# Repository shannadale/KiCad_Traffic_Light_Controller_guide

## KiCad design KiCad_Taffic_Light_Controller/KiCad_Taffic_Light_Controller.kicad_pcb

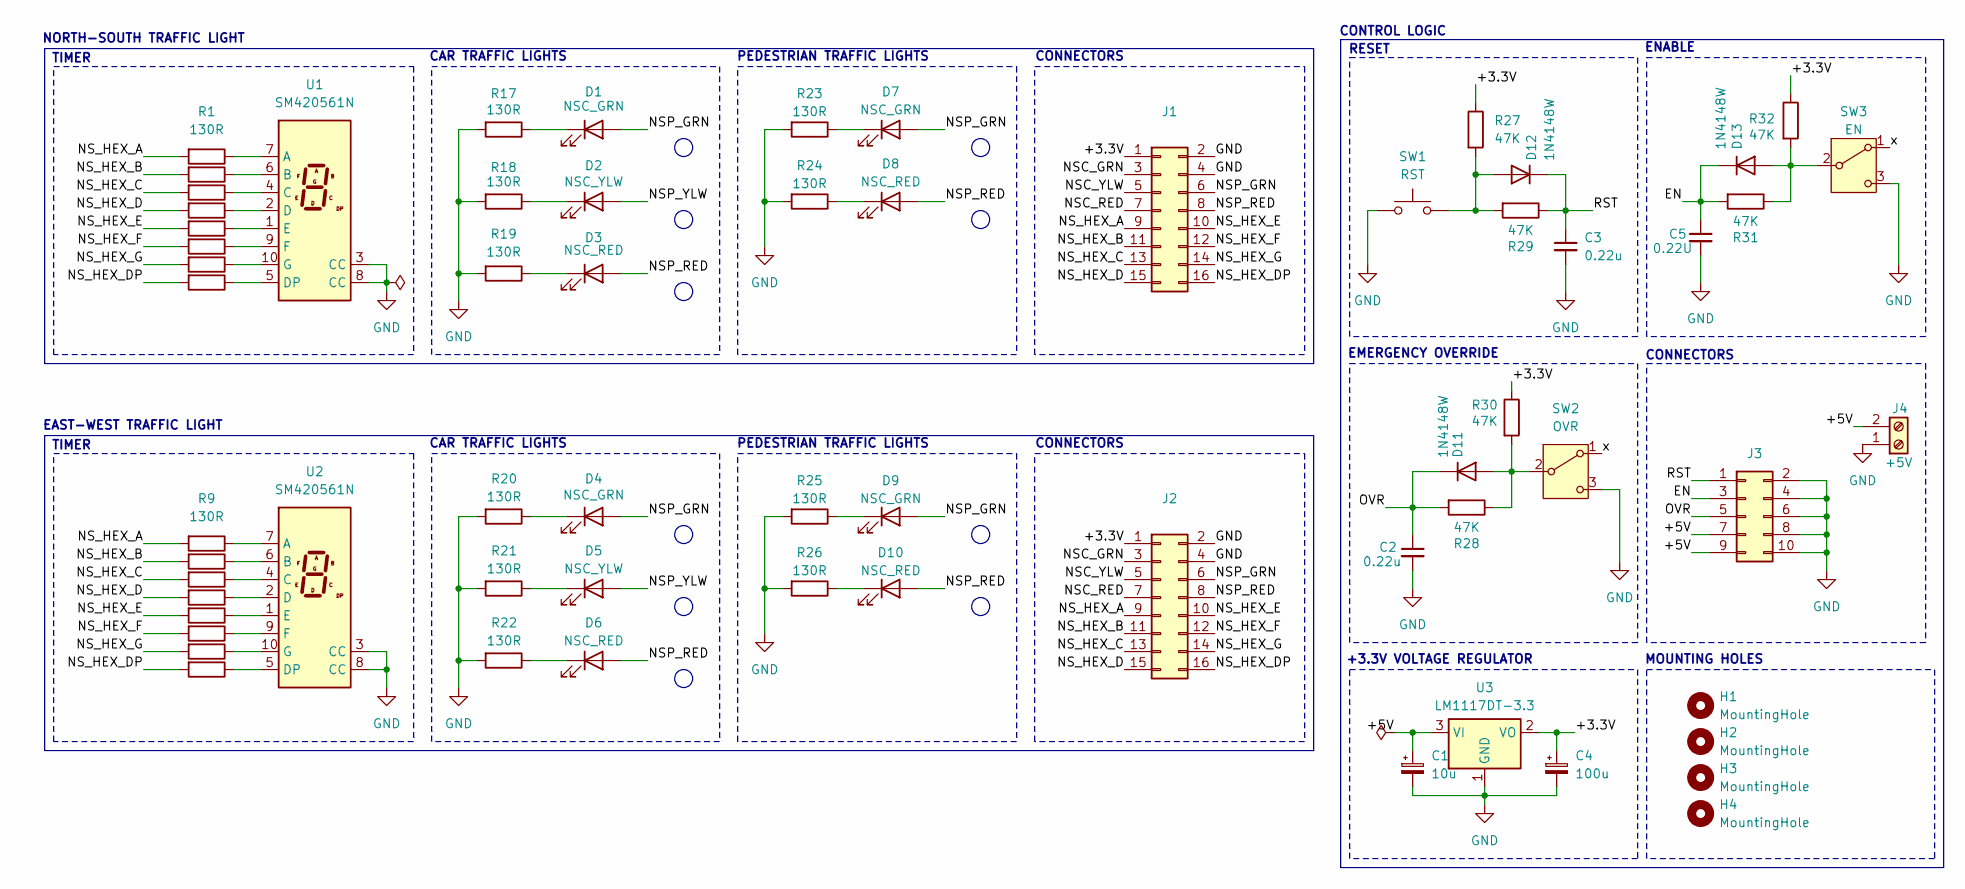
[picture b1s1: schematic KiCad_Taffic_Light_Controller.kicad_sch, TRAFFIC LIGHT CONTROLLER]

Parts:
C1: 10u; CP_Elec_4x5.3
C2, C3: 0.22u; C_1206_3216Metric_Pad1.33x1.80mm_HandSolder
C4: 100u; CP_Elec_6.3x5.8
C5: 0.22U; C_1206_3216Metric_Pad1.33x1.80mm_HandSolder
D1, D4, D7, D9: NSC_GRN; LED_D5.0mm
D2, D5: NSC_YLW; LED_D5.0mm
D3, D6, D8, D10: NSC_RED; LED_D5.0mm
D11, D12, D13: 1N4148W; D_SOD-123
H1, H2, H3, H4: MountingHole; MountingHole_2.2mm_M2
J1: NS Connector; PinHeader_2x08_P2.54mm_Vertical
J2: EW Connector; PinHeader_2x08_P2.54mm_Vertical
J3: Control Logic Connector; PinHeader_2x05_P2.54mm_Vertical
J4: +5V; Terminal_Block_5mm
R1, R2, R3, R4, R5, R6, R7, R8, R9, R10, R11, R12, R13, R14, R15, R16, R17, R18, R19, R20, R21, R22, R23, R24, R25, R26: 130R; R_1206_3216Metric_Pad1.30x1.75mm_HandSolder
R27, R28, R29, R30, R31, R32: 47K; R_1206_3216Metric_Pad1.30x1.75mm_HandSolder
SW1: RST; tact_switch_5mm
SW2: OVR; slide_switch_2.54mm
SW3: EN; slide_switch_2.54mm
U1, U2: SM420561N; 7SegmentLED_LTS6760_LTS6780
U3: LM1117DT-3.3; SOT-223

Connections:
/+3.3V: C4.1, J1.1, J2.1, R27.1, R30.1, R32.1, U3.2 (VO)
/+5V: C1.1, J3.7, J3.9, J4.2, U3.3 (VI)
/EN: C5.1, D13.1 (K), J3.3, R31.2
/NSC_GRN: J1.3, J2.3
/NSC_RED: J1.7, J2.7
/NSC_YLW: J1.5, J2.5
/NSP_GRN: D1.2 (A), D4.2 (A), D7.2 (A), D9.2 (A), J1.6, J2.6
/NSP_RED: D3.2 (A), D6.2 (A), D8.2 (A), D10.2 (A), J1.8, J2.8
/NSP_YLW: D2.2 (A), D5.2 (A)
/NS_HEX_A: J1.9, J2.9, R1.2, R9.2
/NS_HEX_B: J1.11, J2.11, R2.2, R10.2
/NS_HEX_C: J1.13, J2.13, R3.2, R11.2
/NS_HEX_D: J1.15, J2.15, R4.2, R12.2
/NS_HEX_DP: J1.16, J2.16, R8.2, R16.2
/NS_HEX_E: J1.10, J2.10, R5.2, R13.2
/NS_HEX_F: J1.12, J2.12, R6.2, R14.2
/NS_HEX_G: J1.14, J2.14, R7.2, R15.2
/OVR: C2.1, D11.1 (K), J3.5, R28.2
/RST: C3.1, D12.1 (K), J3.1, R29.1
/x: SW2.1 (A), SW3.1 (A)
GND: C1.2, C2.2, C3.2, C4.2, C5.2, J1.2, J1.4, J2.2, J2.4, J3.2, J3.4, J3.6, J3.8, J3.10, J4.1, R17.2, R18.2, R19.2, R20.2, R21.2, R22.2, R23.2, R24.2, R25.2, R26.2, SW1.1, SW2.3 (C), SW3.3 (C), U1.3 (CC), U1.8 (CC), U2.3 (CC), U2.8 (CC), U3.1 (GND)
unnamed: D1.1 (K), R17.1
unnamed: D2.1 (K), R18.1
unnamed: D3.1 (K), R19.1
unnamed: D4.1 (K), R20.1
unnamed: D5.1 (K), R21.1
unnamed: D6.1 (K), R22.1
unnamed: D7.1 (K), R23.1
unnamed: D8.1 (K), R24.1
unnamed: D9.1 (K), R25.1
unnamed: D10.1 (K), R26.1
unnamed: D11.2 (A), R28.1, R30.2, SW2.2 (B)
unnamed: D12.2 (A), R27.2, R29.2, SW1.2
unnamed: D13.2 (A), R31.1, R32.2, SW3.2 (B)
unnamed: R1.1, U1.7 (A)
unnamed: R2.1, U1.6 (B)
unnamed: R3.1, U1.4 (C)
unnamed: R4.1, U1.2 (D)
unnamed: R8.1, U1.5 (DP)
unnamed: R5.1, U1.1 (E)
unnamed: R6.1, U1.9 (F)
unnamed: R7.1, U1.10 (G)
unnamed: R9.1, U2.7 (A)
unnamed: R10.1, U2.6 (B)
unnamed: R11.1, U2.4 (C)
unnamed: R12.1, U2.2 (D)
unnamed: R16.1, U2.5 (DP)
unnamed: R13.1, U2.1 (E)
unnamed: R14.1, U2.9 (F)
unnamed: R15.1, U2.10 (G)

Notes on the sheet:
TIMER
PEDESTRIAN TRAFFIC LIGHTS
CAR TRAFFIC LIGHTS
MOUNTING HOLES
CONNECTORS
NORTH-SOUTH TRAFFIC LIGHT
ENABLE
EAST-WEST TRAFFIC LIGHT
CONNECTORS
+3.3V VOLTAGE REGULATOR
RESET
EMERGENCY OVERRIDE
CONTROL LOGIC

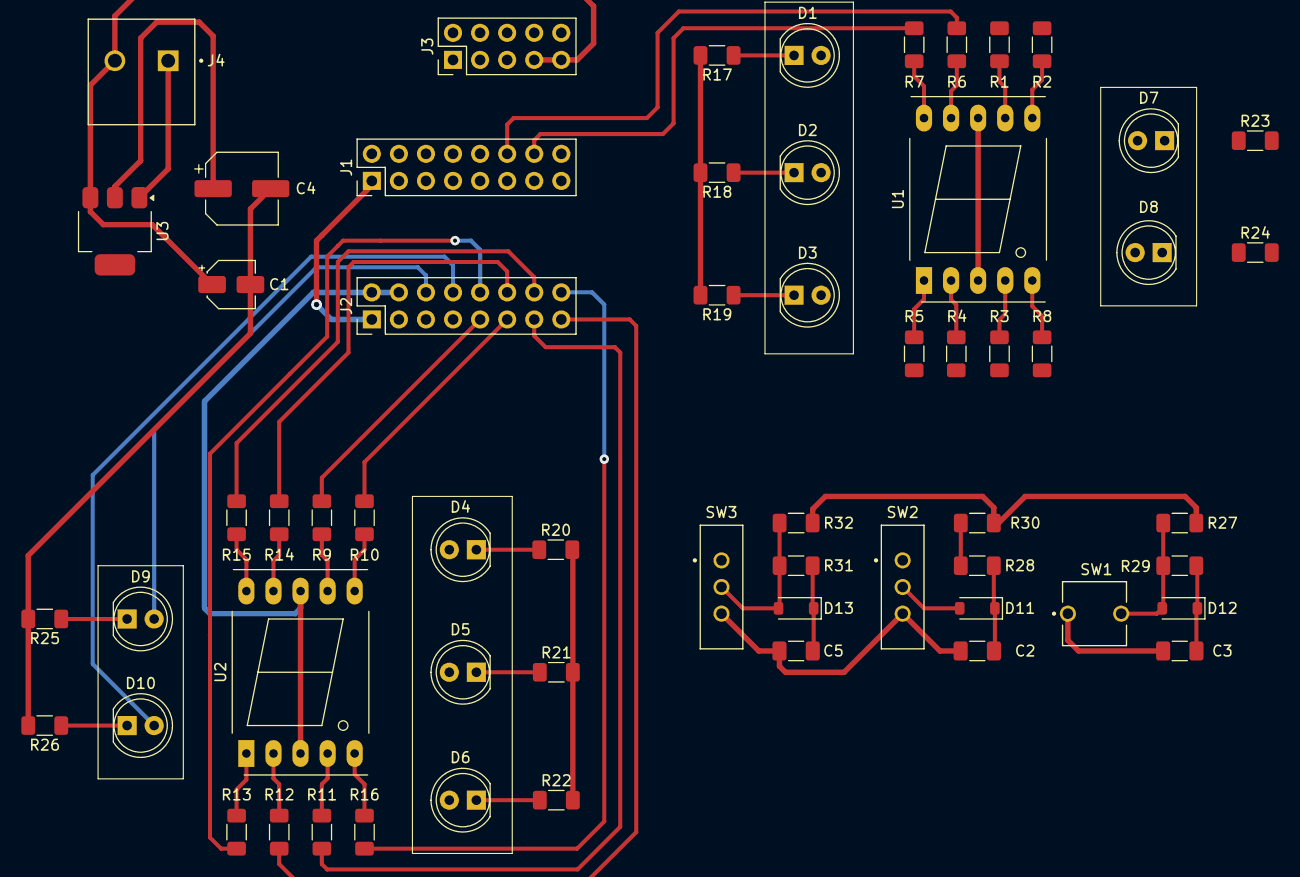
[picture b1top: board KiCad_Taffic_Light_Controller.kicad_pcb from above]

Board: 2 copper layers, 64 parts (0 on the bottom side), 50 nets.

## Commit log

2026-04-16 la pa tapos :((
2026-04-17 4/17/26
2026-04-19 4/19(1pm)
2026-04-19 5:23PM
2026-04-19 anoni
2026-04-19 aukona
2026-04-19 hala
